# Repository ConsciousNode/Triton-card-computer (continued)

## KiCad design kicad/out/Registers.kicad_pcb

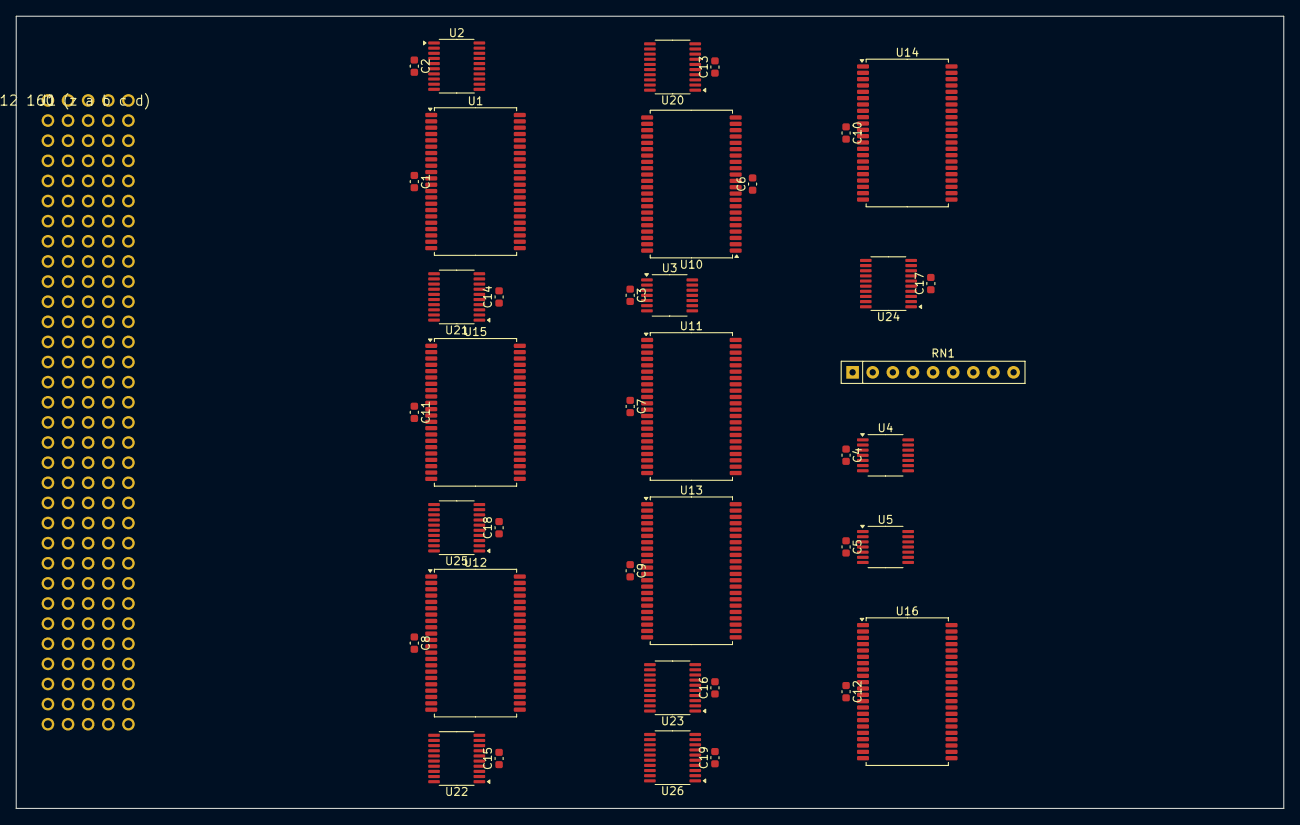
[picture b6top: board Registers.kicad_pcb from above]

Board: 4 copper layers, 160.0 x 100.0 mm, 40 parts (0 on the bottom side), 141 nets, no tracks yet.

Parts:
C1, C2, C3, C4, C5, C6, C7, C8, C9, C10, C11, C12, C13, C14, C15, C16, C17, C18, C19: 100n; C_0603_1608Metric
J1: DIN41612 160 (z a b c d)
RN1: RPACK8; R_Array_SIP9
U1, U10, U11, U12, U13, U14, U15, U16: IS61WV5128; TSOP-II-44_10.16x18.41mm_P0.8mm
U2: LVC574; TSSOP-20_4.4x6.5mm_P0.65mm
U3: LVC32; TSSOP-14_4.4x5mm_P0.65mm
U4: LVC08; TSSOP-14_4.4x5mm_P0.65mm
U5: LVC04; TSSOP-14_4.4x5mm_P0.65mm
U20, U21, U22, U23, U24, U25, U26: LVC245; TSSOP-20_4.4x6.5mm_P0.65mm

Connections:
+3V3: C1.1, C2.1, C3.1, C4.1, C5.1, C6.1, C7.1, C8.1, C9.1, C10.1, C11.1, C12.1, C13.1, C14.1, C15.1, C16.1, C17.1, C18.1, C19.1, J1.z2, J1.z4, J1.z6, J1.z10, J1.z12, J1.z14, J1.z18, J1.z20, J1.z22, J1.z26, J1.z28, J1.z30, RN1.1, U1.11, U1.15, U1.33, U2.20, U3.14, U4.14, U5.14, U10.11, U10.33, U11.11, U11.33, U12.11, U12.33, U13.11, U13.33, U14.11, U14.33, U15.11, U15.33, U16.11, U16.33, U20.20, U21.20, U22.20, U23.20, U24.20, U25.20, U26.20
+5V: J1.z8, J1.z16, J1.z24, J1.z32
/RDE: U3.3, U4.1, U5.1, U10.37, U11.37, U12.37, U13.37, U14.37, U15.37, U16.37
/WEP: U3.11, U10.15, U11.15, U12.15, U13.15, U14.15, U15.15, U16.15
/WRA: U3.6, U3.9
/WRE: U3.8, U3.12, U4.2
/WSTB: J1.d1, U3.13
/XOE: U4.3, U20.19, U21.19, U22.19, U23.19, U24.19, U25.19, U26.19
ABORT: J1.c15, U3.10
CLK: J1.c10, U2.11
CSD0: U1.9, U2.2
CSD1: U1.10, U2.3
CW_/RD: RN1.2, U2.19, U3.1
CW_/WR: RN1.3, U2.18, U3.4
D0+: J1.a1, U20.18
D0-: J1.a2, U20.17
D1+: J1.a3, U20.16
D1-: J1.a4, U20.15
D2+: J1.a5, U20.14
D2-: J1.a6, U20.13
D3+: J1.a7, U20.12
D3-: J1.a9, U20.11
D4+: J1.a10, U21.18
D4-: J1.a11, U21.17
D5+: J1.a12, U21.16
D5-: J1.a13, U21.15
D6+: J1.a14, U21.14
D6-: J1.a15, U21.13
D7+: J1.a17, U21.12
D7-: J1.a18, U21.11
D8+: J1.a19, U22.18
D8-: J1.a20, U22.17
D9+: J1.a21, U22.16
D9-: J1.a22, U22.15
D10+: J1.a23, U22.14
D10-: J1.a25, U22.13
D11+: J1.a26, U22.12
D11-: J1.a27, U22.11
D12+: J1.a28, U23.18
D12-: J1.a29, U23.17
D13+: J1.a30, U23.16
D13-: J1.a31, U23.15
D14+: J1.b1, U23.14
D14-: J1.b2, U23.13
D15+: J1.b3, U23.12
D15-: J1.b4, U23.11
D16+: J1.b5, U24.18
D16-: J1.b6, U24.17
D17+: J1.b7, U24.16
D17-: J1.b9, U24.15
D18+: J1.b10, U24.14
D18-: J1.b11, U24.13
D19+: J1.b12, U24.12
D19-: J1.b13, U24.11
D20+: J1.b14, U25.18
D20-: J1.b15, U25.17
D21+: J1.b17, U25.16
D21-: J1.b18, U25.15
D22+: J1.b19, U25.14
D22-: J1.b20, U25.13
D23+: J1.b21, U25.12
D23-: J1.b22, U25.11
D24+: J1.b23, U26.18
D24-: J1.b25, U26.17
D25+: J1.b26, U26.16
D25-: J1.b27, U26.15
D26+: J1.b28, U26.14
D26-: J1.b29, U26.13
GND: C1.2, C2.2, C3.2, C4.2, C5.2, C6.2, C7.2, C8.2, C9.2, C10.2, C11.2, C12.2, C13.2, C14.2, C15.2, C16.2, C17.2, C18.2, C19.2, J1.a8, J1.a16, J1.a24, J1.a32, J1.b8, J1.b16, J1.b24, J1.b32, J1.c8, J1.c16, J1.c24, J1.c32, J1.d8, J1.d16, J1.d24, J1.d32, J1.z1, J1.z3, J1.z5, J1.z7, J1.z9, J1.z11, J1.z13, J1.z15, J1.z17, J1.z19, J1.z21, J1.z23, J1.z25, J1.z27, J1.z29, J1.z31, U1.8, U1.12, U1.26, U1.27, U1.28, U1.29, U1.30, U1.34, U1.37, U1.38, U1.39, U1.40, U1.41, U2.4, U2.5, U2.6, U2.7, U2.8, U2.9, U2.10, U3.7, U4.4, U4.5, U4.7, U4.9, U4.10, U4.12, U4.13, U5.7, U10.8, U10.12, U10.16, U10.17, U10.18, U10.19, U10.20, U10.26, U10.27, U10.28, U10.29, U10.30, U10.34, U10.38, U10.39, U10.40, U10.41, U11.8, U11.12, U11.16, U11.17, U11.18, U11.19, U11.20, U11.26, U11.27, U11.28, U11.29, U11.30, U11.34, U11.38, U11.39, U11.40, U11.41, U12.8, U12.12, U12.16, U12.17, U12.18, U12.19, U12.20, U12.26, U12.27, U12.28, U12.29, U12.30, U12.34, U12.38, U12.39, U12.40, U12.41, U13.8, U13.12, U13.16, U13.17, U13.18, U13.19, U13.20, U13.26, U13.27, U13.28, U13.29, U13.30, U13.34, U13.38, U13.39, U13.40, U13.41, U14.8, U14.12, U14.16, U14.17, U14.18, U14.19, U14.20, U14.26, U14.27, U14.28, U14.29, U14.30, U14.34, U14.38, U14.39, U14.40, U14.41, U15.8, U15.12, U15.16, U15.17, U15.18, U15.19, U15.20, U15.26, U15.27, U15.28, U15.29, U15.30, U15.34, U15.38, U15.39, U15.40, U15.41, U16.8, U16.12, U16.16, U16.17, U16.18, U16.19, U16.20, U16.26, U16.27, U16.28, U16.29, U16.30, U16.34, U16.38, U16.39, U16.40, U16.41, U20.10, U21.10, U22.10, U23.10, U24.10, U25.10, U26.8, U26.9, U26.10
M0+: U10.9, U20.2
M0-: U10.10, U20.3
M1+: U10.13, U20.4
M1-: U10.14, U20.5
M2+: U10.31, U20.6
M2-: U10.32, U20.7
M3+: U10.35, U20.8
M3-: U10.36, U20.9
M4+: U11.9, U21.2
M4-: U11.10, U21.3
M5+: U11.13, U21.4
M5-: U11.14, U21.5
M6+: U11.31, U21.6
M6-: U11.32, U21.7
M7+: U11.35, U21.8
M7-: U11.36, U21.9
M8+: U12.9, U22.2
M8-: U12.10, U22.3
M9+: U12.13, U22.4
M9-: U12.14, U22.5
M10+: U12.31, U22.6
M10-: U12.32, U22.7
M11+: U12.35, U22.8
M11-: U12.36, U22.9
M12+: U13.9, U23.2
M12-: U13.10, U23.3
M13+: U13.13, U23.4
M13-: U13.14, U23.5
M14+: U13.31, U23.6
M14-: U13.32, U23.7
M15+: U13.35, U23.8
M15-: U13.36, U23.9
M16+: U14.9, U24.2
M16-: U14.10, U24.3
M17+: U14.13, U24.4
M17-: U14.14, U24.5
M18+: U14.31, U24.6
M18-: U14.32, U24.7
M19+: U14.35, U24.8
M19-: U14.36, U24.9
M20+: U15.9, U25.2
M20-: U15.10, U25.3
M21+: U15.13, U25.4
M21-: U15.14, U25.5
M22+: U15.31, U25.6
M22-: U15.32, U25.7
M23+: U15.35, U25.8
M23-: U15.36, U25.9
M24+: U16.9, U26.2
M24-: U16.10, U26.3
M25+: U16.13, U26.4
M25-: U16.14, U26.5
M26+: U16.31, U26.6
M26-: U16.32, U26.7
RESET: J1.c12, U2.1
RSLOT0: J1.d11, U10.3, U11.3, U12.3, U13.3, U14.3, U15.3, U16.3
RSLOT1: J1.d12, U10.4, U11.4, U12.4, U13.4, U14.4, U15.4, U16.4
RSLOT2: J1.d13, U10.5, U11.5, U12.5, U13.5, U14.5, U15.5, U16.5
RSLOT3: J1.d14, U10.6, U11.6, U12.6, U13.6, U14.6, U15.6, U16.6
RSLOT4: J1.d15, U10.7, U11.7, U12.7, U13.7, U14.7, U15.7, U16.7
SPRNR: J1.c18, U3.2, U3.5
UA0: J1.b30, U1.3
UA1: J1.b31, U1.4
UA2: J1.c1, U1.5
UA3: J1.c2, U1.6
UA4: J1.c3, U1.7
UA5: J1.c4, U1.16
UA6: J1.c5, U1.17
UA7: J1.c6, U1.18
UA8: J1.c7, U1.19
UA9: J1.c9, U1.20
XDIR: U5.2, U20.1, U21.1, U22.1, U23.1, U24.1, U25.1, U26.1
